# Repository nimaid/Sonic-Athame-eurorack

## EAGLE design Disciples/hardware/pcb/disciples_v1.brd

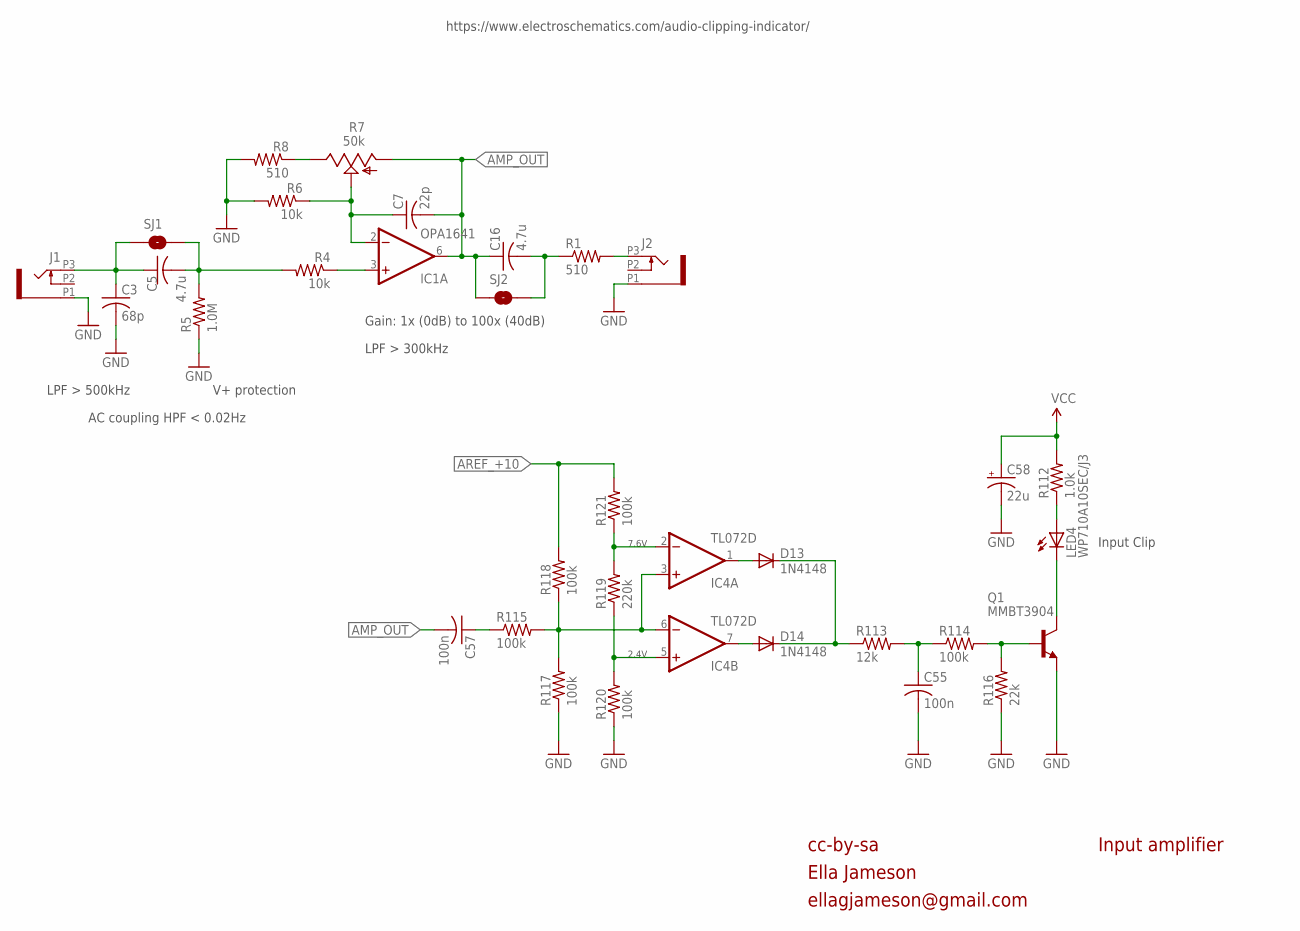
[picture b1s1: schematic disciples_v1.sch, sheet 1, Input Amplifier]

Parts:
C3: 68p; C0402
C5, C16: 4.7u; C0603
C7: 22p; C0402
C55, C57: 100n; C0603
C58: 22u; PANASONIC_C
D13, D14: 1N4148; SOD323-W
IC1: OPA1641; MSOP8
IC4: TL072D; SO08
J1, J2: PJ301_THONKICONN6; WQP_PJ_301M6
LED4: WP710A10SEC/J3; LED3MM
Q1: MMBT3904; SOT23-BEC
R1, R8: 510; R0402
R4, R6: 10k; R0402
R5: 1.0M; R0402
R7: 50k; ALPS_POT_VERTICAL_PS
R112: 1.0k; R0603
R113: 12k; R0603
R114, R115, R117, R118, R120, R121: 100k; R0603
R116: 22k; R0603
R119: 220k; R0603
SJ1, SJ2: SOLDERJUMPERNC; SJ_2S

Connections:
AMP_OUT: C7.2, C16.1, C57.2, IC1.6 (OUT), R7.P$3 (A), SJ2.1; also elsewhere on the board
AREF_+10: R118.2, R121.2; also elsewhere on the board
GND: C3.2, C55.2, C58.-, J1.P1 (1), J2.P1 (1), Q1.E, R5.1, R6.2, R8.2, R116.1, R117.1, R120.1; also elsewhere on the board
unnamed: IC1.3 (+IN), R4.1
unnamed: J2.P3 (3), R1.2
unnamed: C3.1, C5.1, J1.P3 (3), SJ1.1
unnamed: C7.1, IC1.2 (-IN), R6.1, R7.P$2 (S)
unnamed: C5.2, R4.2, R5.2, SJ1.2
unnamed: R7.P$1 (E), R8.1
unnamed: C16.2, R1.1, SJ2.2
unnamed: LED4.K (C), Q1.C
unnamed: C57.1, R115.1
unnamed: IC4.3 (+IN), IC4.6 (-IN), R115.2, R117.2, R118.1
unnamed: IC4.2 (-IN), R119.2, R121.1
unnamed: C55.1, R113.2, R114.1
unnamed: IC4.5 (+IN), R119.1, R120.2
unnamed: D13.A, IC4.1 (OUT)
unnamed: D14.A, IC4.7 (OUT)
unnamed: D13.C, D14.C, R113.1
unnamed: LED4.A, R112.1
unnamed: Q1.B, R114.2, R116.2
VCC: C58.+, R112.2; also elsewhere on the board

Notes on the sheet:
cc-by-sa
Input amplifier
Gain: 1x (0dB) to 100x (40dB)
LPF > 500kHz
V+ protection
LPF > 300kHz
AC coupling HPF < 0.02Hz
Ella Jameson
ellagjameson@gmail.com
2.4V
7.6V
Input Clip
https://www.electroschematics.com/audio-clipping-indicator/

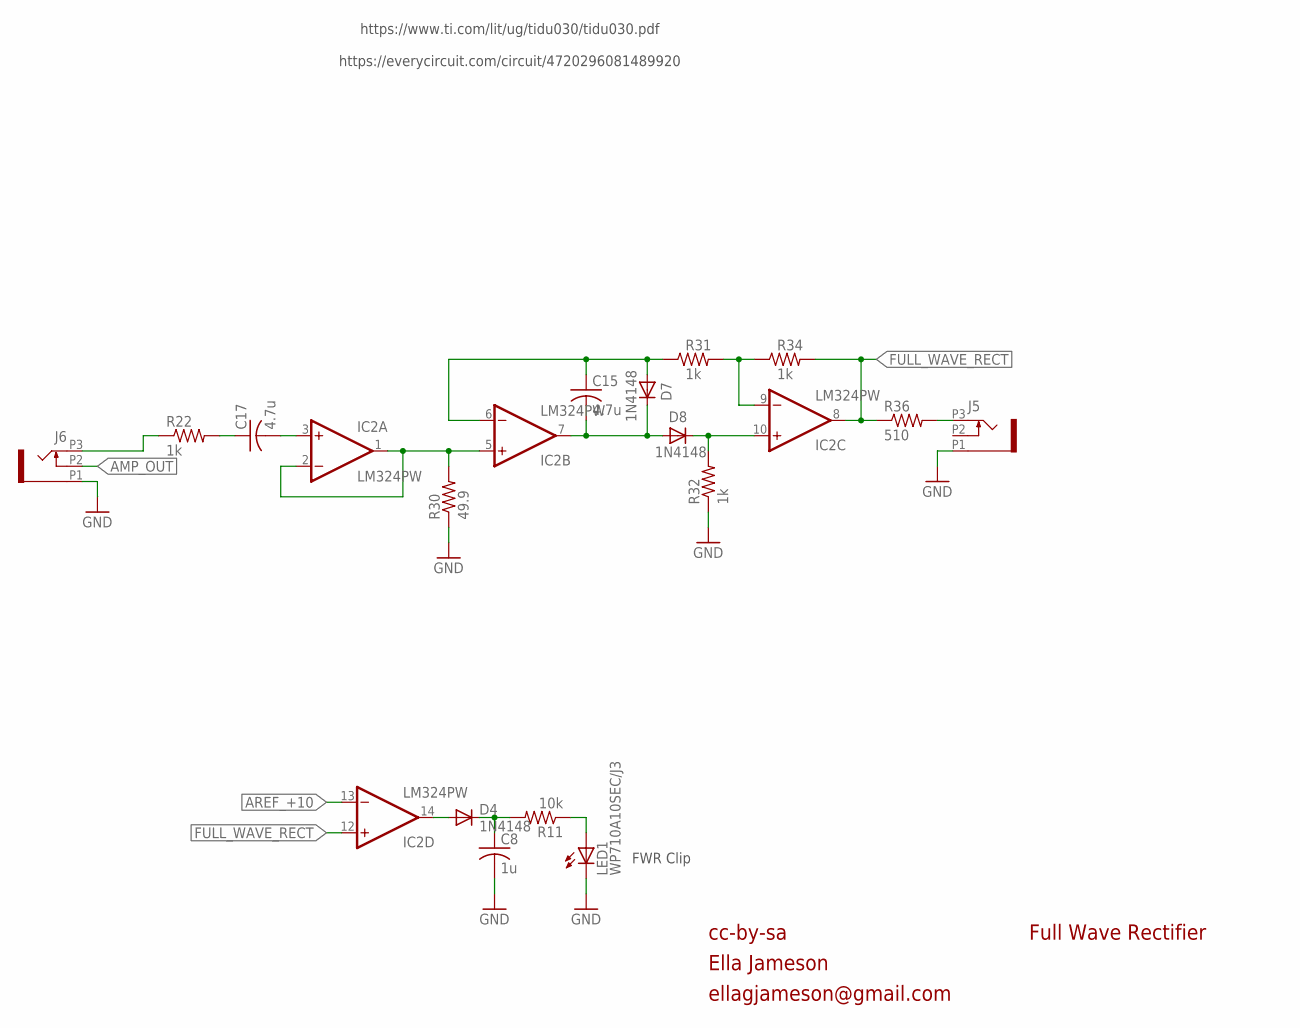
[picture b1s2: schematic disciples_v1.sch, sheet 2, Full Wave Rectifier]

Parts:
C8: 1u; C0402
C15, C17: 4.7u; C0603
D4, D7, D8: 1N4148; SOD523
IC2: LM324PW; TSSOP14
J5, J6: PJ301_THONKICONN6; WQP_PJ_301M6
LED1: WP710A10SEC/J3; LED3MM
R11: 10k; R0402
R22, R31, R32, R34: 1k; R0402
R30: 49.9; R0402
R36: 510; R0402

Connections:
AMP_OUT: J6.P2 (2); also elsewhere on the board
AREF_+10: IC2.13 (-IN); also elsewhere on the board
FULL_WAVE_RECT: IC2.8 (OUT), IC2.12 (+IN), R34.2, R36.1; also elsewhere on the board
FWR_CLIP: D4.A, IC2.14 (OUT)
GND: C8.2, J5.P1 (1), J6.P1 (1), LED1.K (C), R30.1, R32.1; also elsewhere on the board
unnamed: C15.2, D7.C, D8.A, IC2.7 (OUT)
unnamed: J5.P3 (3), R36.2
unnamed: C15.1, D7.A, IC2.6 (-IN), R31.1
unnamed: D8.C, IC2.10 (+IN), R32.2
unnamed: IC2.9 (-IN), R31.2, R34.1
unnamed: C17.1, R22.2
unnamed: C8.1, D4.C, R11.2
unnamed: LED1.A, R11.1
unnamed: C17.2, IC2.3 (+IN)
unnamed: IC2.1 (OUT), IC2.2 (-IN), IC2.5 (+IN), R30.2
unnamed: J6.P3 (3), R22.1

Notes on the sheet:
cc-by-sa
Full Wave Rectifier
Ella Jameson
ellagjameson@gmail.com
https://www.ti.com/lit/ug/tidu030/tidu030.pdf https://everycircuit.com/circuit/4720296081489920
FWR Clip

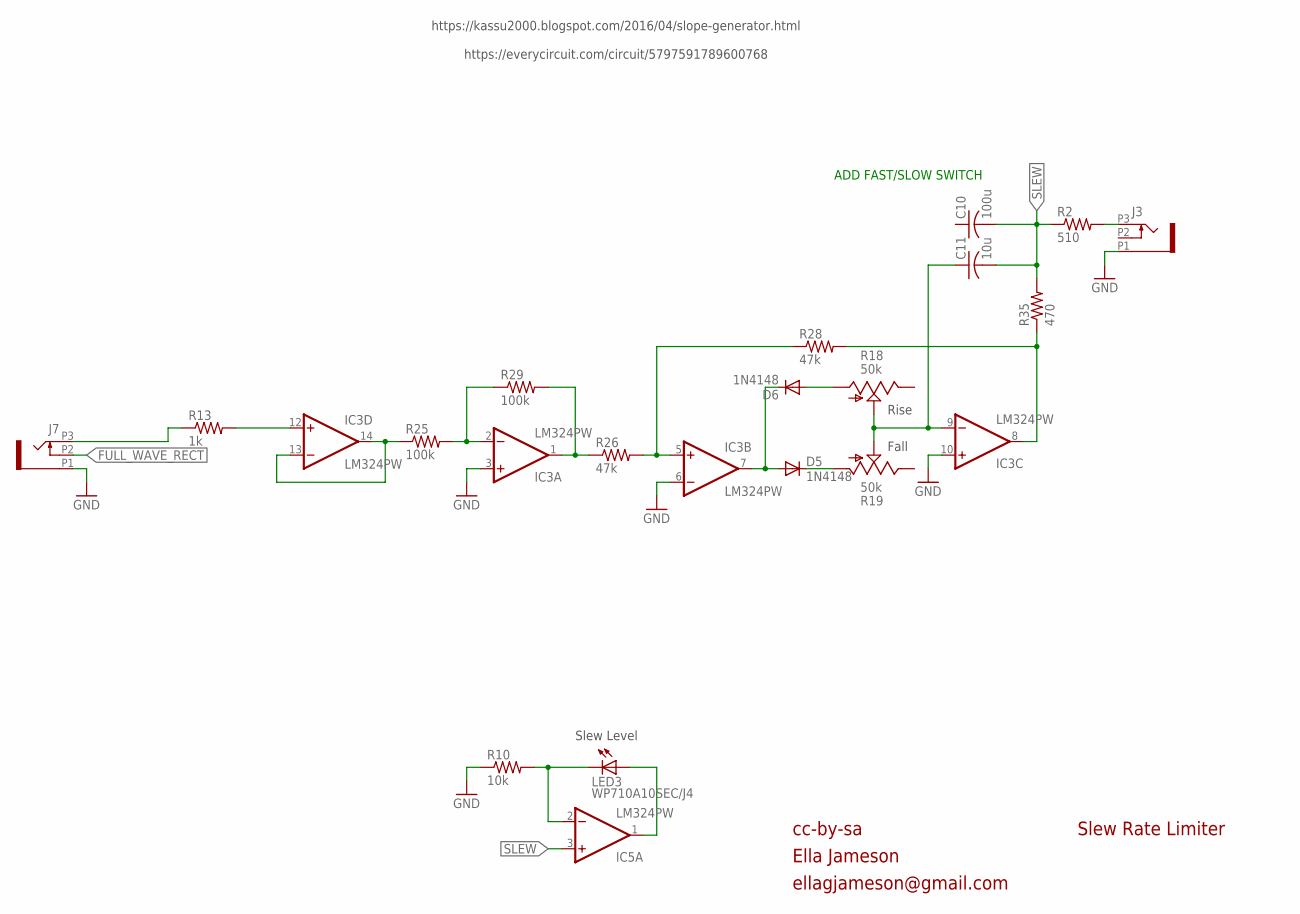
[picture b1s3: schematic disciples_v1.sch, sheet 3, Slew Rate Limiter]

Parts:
C10: 100u; C0402
C11: 10u; C0402
D5, D6: 1N4148; SOD523
IC3, IC5: LM324PW; TSSOP14
J3, J7: PJ301_THONKICONN6; WQP_PJ_301M6
LED3: WP710A10SEC/J4; LED3MM
R2: 510; R0402
R10: 10k; R0402
R13: 1k; R0402
R18, R19: 50k; ALPS_POT_VERTICAL_PS
R25, R29: 100k; R0402
R26, R28: 47k; R0402
R35: 470; R0402

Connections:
FULL_WAVE_RECT: J7.P2 (2); also elsewhere on the board
GND: IC3.3 (+IN), IC3.6 (-IN), IC3.10 (+IN), J3.P1 (1), J7.P1 (1), R10.1; also elsewhere on the board
unnamed: J7.P3 (3), R13.1
unnamed: IC3.13 (-IN), IC3.14 (OUT), R25.1
unnamed: J3.P3 (3), R2.2
unnamed: IC5.2 (-IN), LED3.K (C), R10.2
unnamed: IC3.2 (-IN), R25.2, R29.1
unnamed: IC3.1 (OUT), R26.1, R29.2
unnamed: IC3.5 (+IN), R26.2, R28.1
unnamed: D5.A, D6.C, IC3.7 (OUT)
unnamed: D5.C, R19.P$3 (A)
unnamed: D6.A, R18.P$3 (A)
unnamed: C11.1, IC3.9 (-IN), R18.P$2 (S), R19.P$2 (S)
unnamed: IC3.12 (+IN), R13.2
unnamed: IC5.1 (OUT), LED3.A
unnamed: IC3.8 (OUT), R28.2, R35.1
SLEW: C10.2, C11.2, IC5.3 (+IN), R2.1, R35.2; also elsewhere on the board

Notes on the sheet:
cc-by-sa
Slew Rate Limiter
https://kassu2000.blogspot.com/2016/04/slope-generator.html https://everycircuit.com/circuit/5797591789600768
Ella Jameson
ellagjameson@gmail.com
Fall
Slew Level
Rise
ADD FAST/SLOW SWITCH

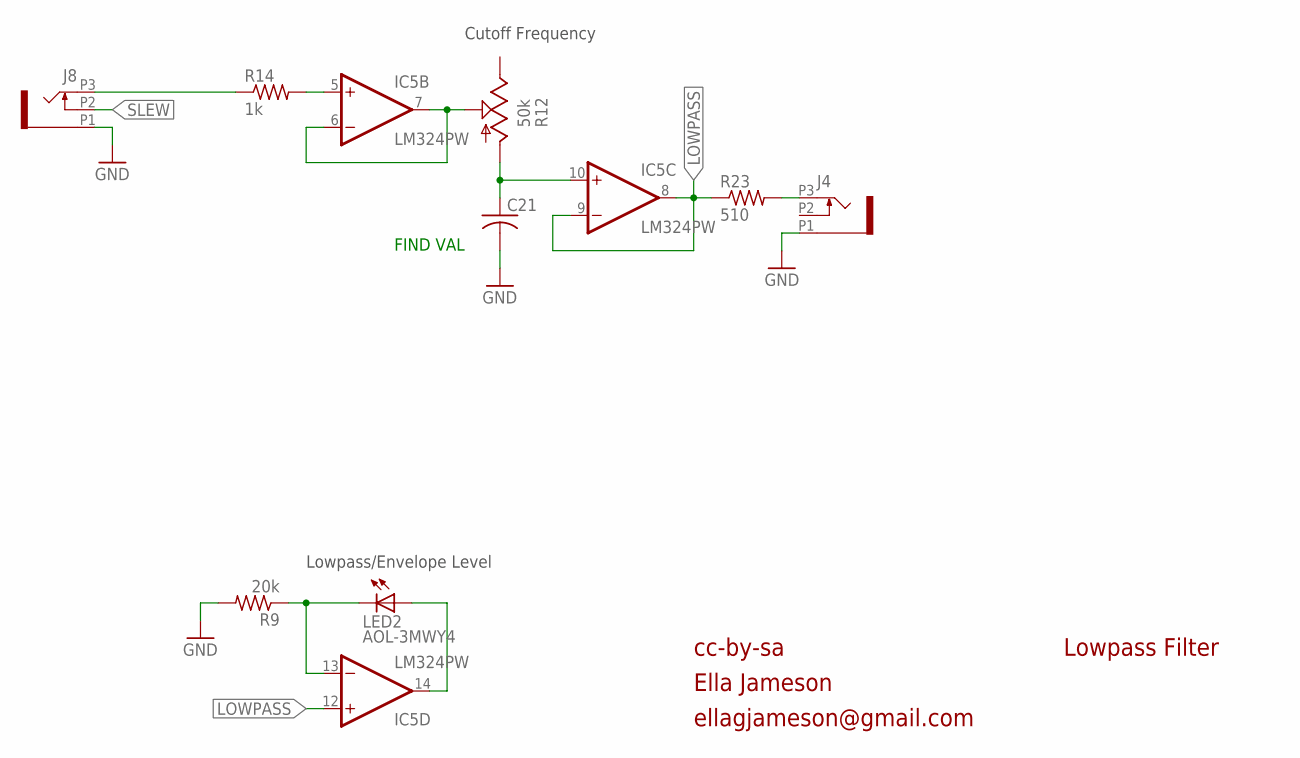
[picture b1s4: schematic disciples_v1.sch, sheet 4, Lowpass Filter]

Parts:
C21: C-USC0402; C0402
IC5: LM324PW; TSSOP14
J4, J8: PJ301_THONKICONN6; WQP_PJ_301M6
LED2: AOL-3MWY4; LED3MM
R9: 20k; R0402
R12: 50k; ALPS_POT_VERTICAL_PS
R14: 1k; R0402
R23: 510; R0402

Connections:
GND: C21.2, J4.P1 (1), J8.P1 (1), R9.2; also elsewhere on the board
LOWPASS: IC5.8 (OUT), IC5.9 (-IN), IC5.12 (+IN), R23.1; also elsewhere on the board
unnamed: C21.1, IC5.10 (+IN), R12.P$3 (A)
unnamed: IC5.5 (+IN), R14.2
unnamed: J8.P3 (3), R14.1
unnamed: J4.P3 (3), R23.2
unnamed: IC5.6 (-IN), IC5.7 (OUT), R12.P$2 (S)
unnamed: IC5.14 (OUT), LED2.A
unnamed: IC5.13 (-IN), LED2.K (C), R9.1
SLEW: J8.P2 (2); also elsewhere on the board

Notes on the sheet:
cc-by-sa
Lowpass Filter
Ella Jameson
ellagjameson@gmail.com
FIND VAL
Lowpass/Envelope Level
Cutoff Frequency

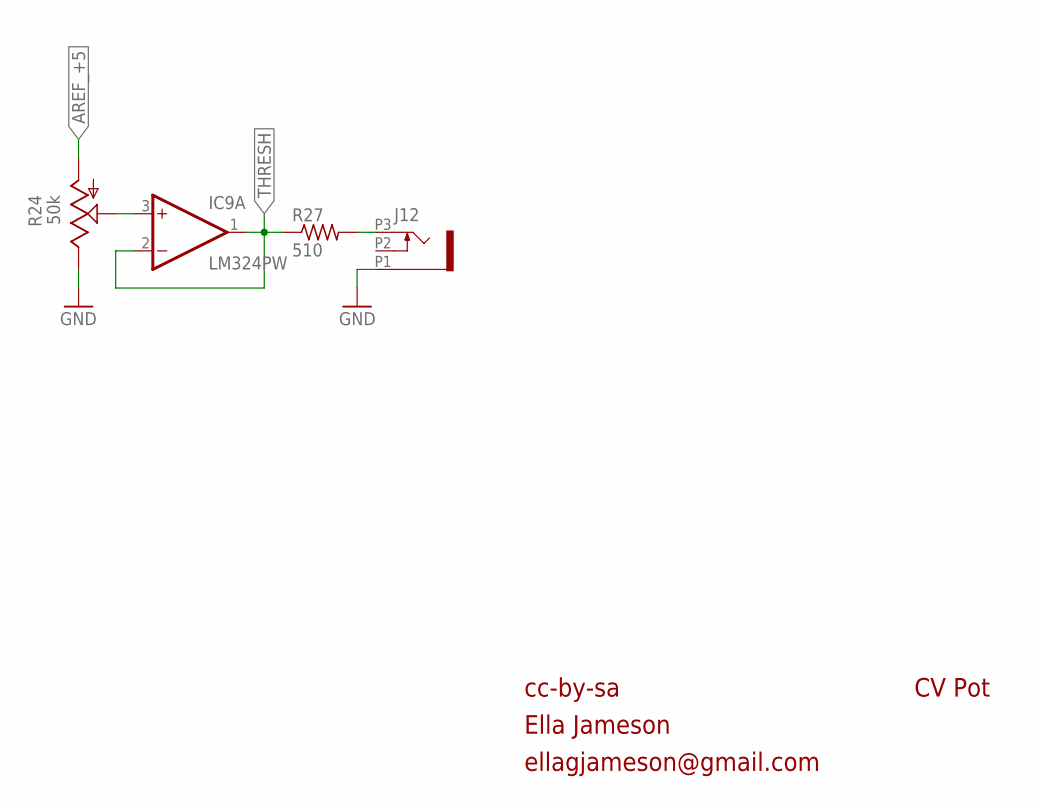
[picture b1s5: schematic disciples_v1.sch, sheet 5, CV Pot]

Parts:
IC9: LM324PW; TSSOP14
J12: PJ301_THONKICONN6; WQP_PJ_301M6
R24: 50k; ALPS_POT_VERTICAL_PS
R27: 510; R0402

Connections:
AREF_+5: R24.P$3 (A); also elsewhere on the board
GND: J12.P1 (1), R24.P$1 (E); also elsewhere on the board
unnamed: IC9.3 (+IN), R24.P$2 (S)
unnamed: J12.P3 (3), R27.2
THRESH: IC9.1 (OUT), IC9.2 (-IN), R27.1; also elsewhere on the board

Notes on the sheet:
cc-by-sa
CV Pot
Ella Jameson
ellagjameson@gmail.com

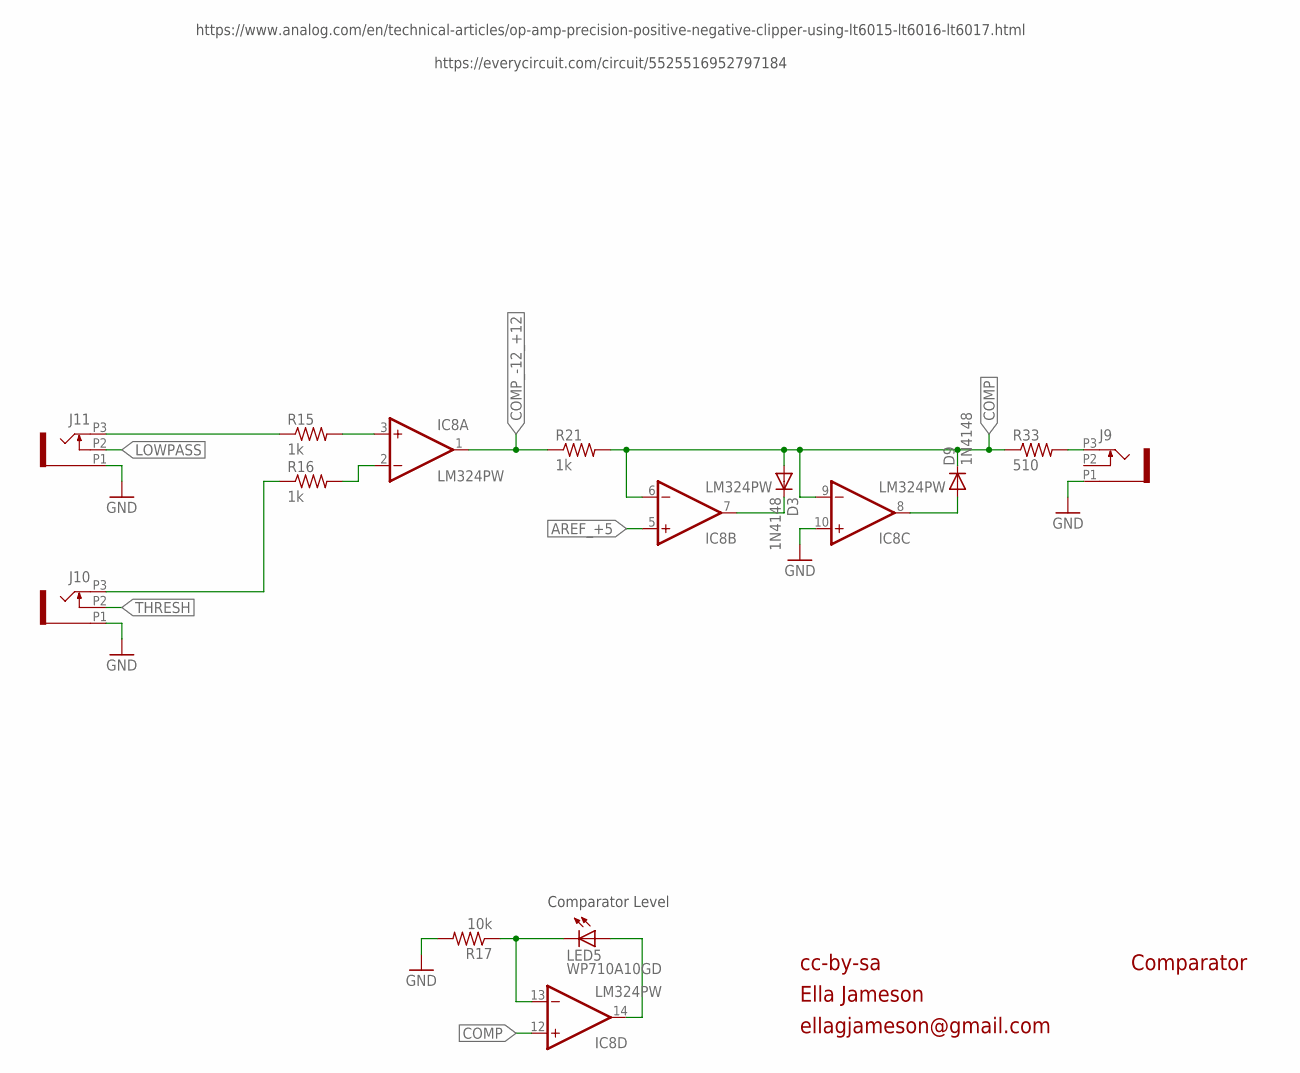
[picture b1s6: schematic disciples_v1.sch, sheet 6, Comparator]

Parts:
D3, D9: 1N4148; SOD523
IC8: LM324PW; TSSOP14
J9, J10, J11: PJ301_THONKICONN6; WQP_PJ_301M6
LED5: WP710A10GD; LED3MM
R15, R16, R21: 1k; R0402
R17: 10k; R0402
R33: 510; R0402

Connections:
AREF_+5: IC8.5 (+IN); also elsewhere on the board
COMP: D3.A, D9.C, IC8.6 (-IN), IC8.9 (-IN), IC8.12 (+IN), R21.2, R33.1
COMP_-12_+12: IC8.1 (OUT), R21.1
GND: IC8.10 (+IN), J9.P1 (1), J10.P1 (1), J11.P1 (1), R17.2; also elsewhere on the board
LOWPASS: J11.P2 (2); also elsewhere on the board
unnamed: J9.P3 (3), R33.2
unnamed: IC8.13 (-IN), LED5.K (C), R17.1
unnamed: IC8.14 (OUT), LED5.A
unnamed: J11.P3 (3), R15.1
unnamed: J10.P3 (3), R16.1
unnamed: IC8.2 (-IN), R16.2
unnamed: IC8.3 (+IN), R15.2
unnamed: D3.C, IC8.7 (OUT)
unnamed: D9.A, IC8.8 (OUT)
THRESH: J10.P2 (2); also elsewhere on the board

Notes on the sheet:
cc-by-sa
Comparator
Ella Jameson
ellagjameson@gmail.com
Comparator Level
https://www.analog.com/en/technical-articles/op-amp-precision-positive-negative-clipper-using-lt6015-lt6016-lt6017.html https://everycircuit.com/circuit/5525516952797184

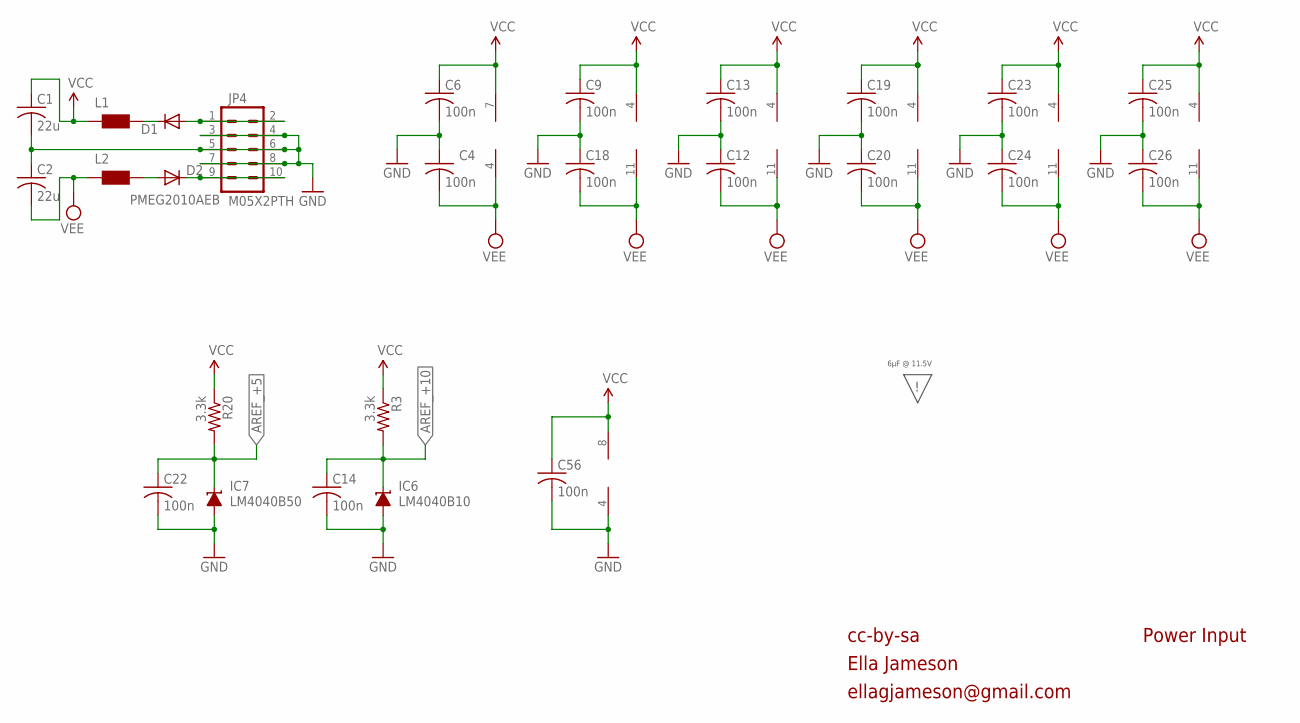
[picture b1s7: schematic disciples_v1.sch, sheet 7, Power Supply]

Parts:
C1, C2: 22u; C1206
C4, C6, C9, C12, C13, C18, C19, C20, C23, C24, C25, C26: 100n; C0402
C14, C22, C56: 100n; C0603
D1, D2: PMEG2010AEB; SOD523
IC1: OPA1641; MSOP8
IC2, IC3, IC5, IC8, IC9: LM324PW; TSSOP14
IC4: TL072D; SO08
IC6: LM4040B10; DBZ_R-PDSO-G3
IC7: LM4040B50; DBZ_R-PDSO-G3
JP4: M05X2PTH; AVR_ICSP
L1, L2: WE-CBF_0603; 0603
R3, R20: 3.3k; R0603

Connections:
AREF_+5: C22.1, IC7.1 (C), R20.2; also elsewhere on the board
AREF_+10: C14.1, IC6.1 (C), R3.2; also elsewhere on the board
GND: C1.2, C2.1, C4.1, C6.2, C9.2, C12.1, C13.2, C14.2, C18.1, C19.2, C20.1, C22.2, C23.2, C24.1, C25.2, C26.1, C56.2, IC4.4 (V-), IC6.2 (A), IC7.2 (A), JP4.3, JP4.4, JP4.5, JP4.6, JP4.7, JP4.8; also elsewhere on the board
unnamed: D1.A, JP4.1, JP4.2
unnamed: D2.C, JP4.9, JP4.10
unnamed: D1.C, L1.2
unnamed: D2.A, L2.2
VCC: C1.1, C6.1, C9.1, C13.1, C19.1, C23.1, C25.1, C56.1, IC1.7 (V+), IC2.4 (V+), IC3.4 (V+), IC4.8 (V+), IC5.4 (V+), IC8.4 (V+), IC9.4 (V+), L1.1, R3.1, R20.1; also elsewhere on the board
VEE: C2.2, C4.2, C12.2, C18.2, C20.2, C24.2, C26.2, IC1.4 (V-), IC2.11 (V-), IC3.11 (V-), IC5.11 (V-), IC8.11 (V-), IC9.11 (V-), L2.1

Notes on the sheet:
cc-by-sa
Power Input
6µF @ 11.5V
Ella Jameson
ellagjameson@gmail.com

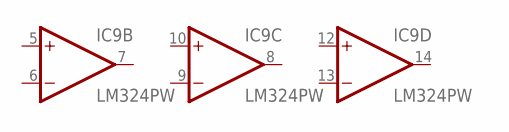
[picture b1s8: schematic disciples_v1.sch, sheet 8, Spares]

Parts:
IC9: LM324PW; TSSOP14

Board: 2 copper layers, 120 parts (2 on the bottom side), 78 nets, no tracks yet.

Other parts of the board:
U$2: ROHS

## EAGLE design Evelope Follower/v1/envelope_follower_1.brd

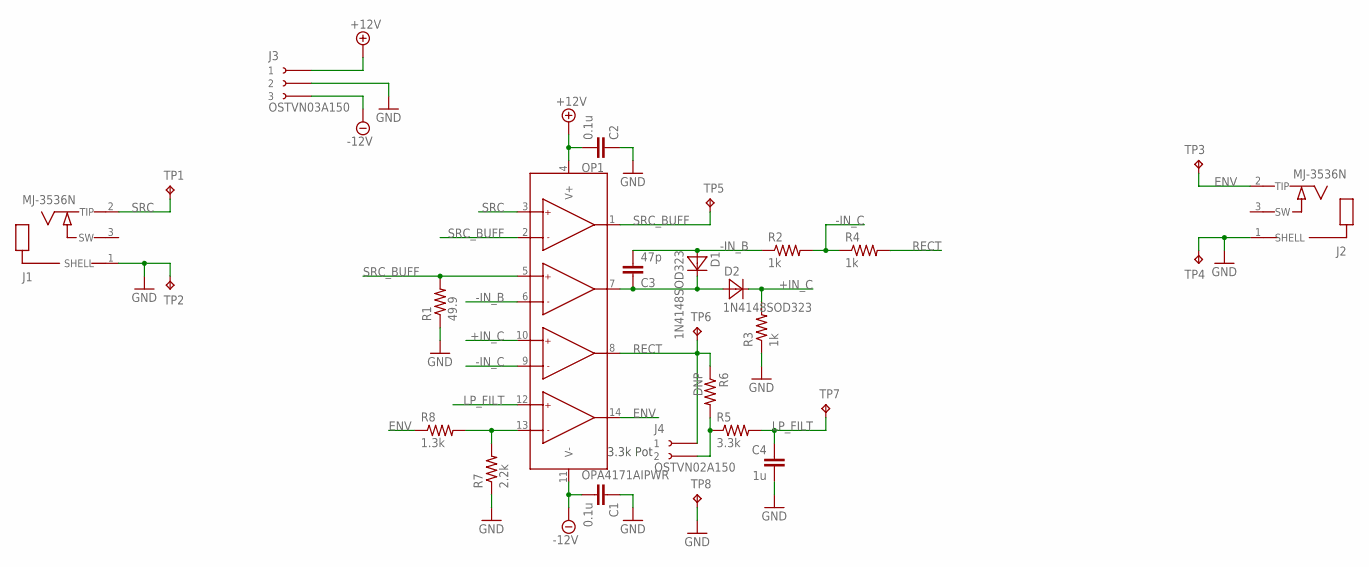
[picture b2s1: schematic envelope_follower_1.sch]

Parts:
C1, C2: 0.1u; C0603
C3: 47p; C0603
C4: 1u; C0603
D1, D2: 1N4148SOD323; SOD323
J1, J2: MJ-3536N
J3: OSTVN03A150
J4: OSTVN02A150
OP1: OPA4171AIPWR; SOP65P640X120-14
R1: 49.9; R0603
R2, R3, R4: 1k; R0603
R5: 3.3k; R0603
R6: DNP; R0603
R7: 2.2k; R0603
R8: 1.3k; R0603
TP1, TP2, TP3, TP4, TP5, TP6, TP7, TP8: TP_THM_1.6_S

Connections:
+12V: C2.2, J3.P$1 (1), OP1.4 (V+)
+IN_C: D2.C, OP1.10 (+IN_C), R3.2
-12V: C1.2, J3.P$3 (3), OP1.11 (V-)
-IN_B: C3.2, D1.A, OP1.6 (-IN_B), R2.1
-IN_C: OP1.9 (-IN_C), R2.2, R4.1
ENV: J2.2 (TIP), OP1.14 (OUT_D), R8.1, TP3.P$1
GND: C1.1, C2.1, C4.2, J1.1 (SHELL), J2.1 (SHELL), J3.P$2 (2), R1.1, R3.1, R7.1, TP2.P$1, TP4.P$1, TP8.P$1
LP_FILT: C4.1, OP1.12 (+IN_D), R5.2, TP7.P$1
unnamed: C3.1, D1.C, D2.A, OP1.7 (OUT_B)
unnamed: J4.P$2 (2), R5.1, R6.2
unnamed: OP1.13 (-IN_D), R7.2, R8.2
RECT: J4.P$1 (1), OP1.8 (OUT_C), R4.2, R6.1, TP6.P$1
SRC: J1.2 (TIP), OP1.3 (+IN_A), TP1.P$1
SRC_BUFF: OP1.1 (OUT_A), OP1.2 (-IN_A), OP1.5 (+IN_B), R1.2, TP5.P$1

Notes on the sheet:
3.3k Pot

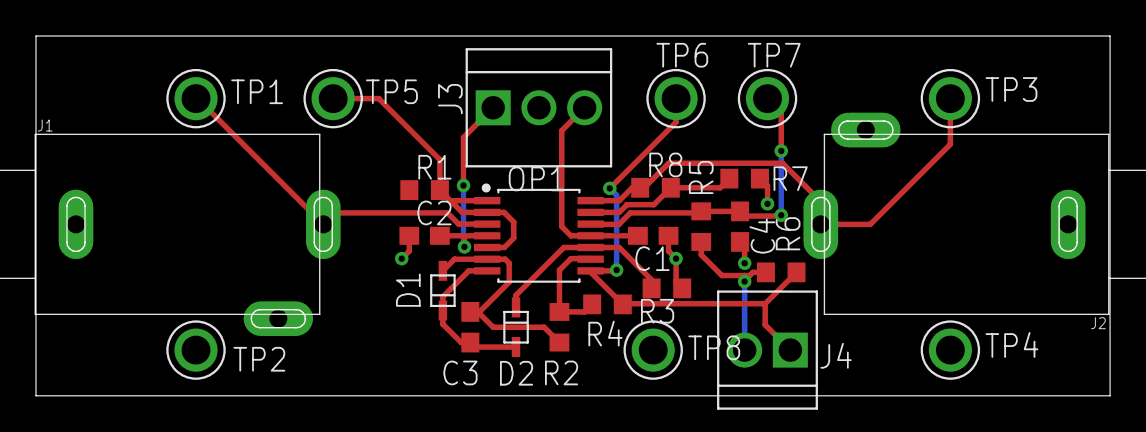
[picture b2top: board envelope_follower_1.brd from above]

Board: 2 copper layers, 59.7 x 20.0 mm, 27 parts (0 on the bottom side), 14 nets.

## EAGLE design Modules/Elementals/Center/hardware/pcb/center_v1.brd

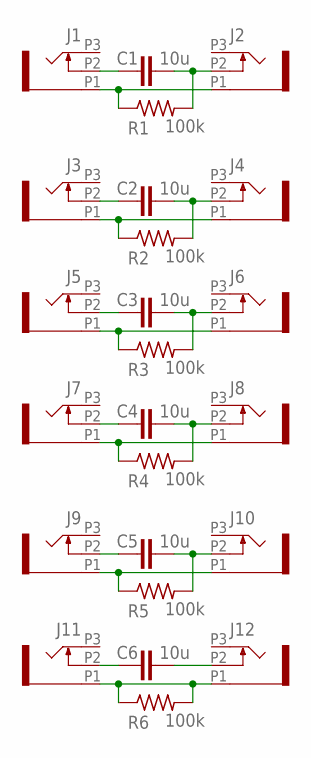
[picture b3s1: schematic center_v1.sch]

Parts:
C1, C2, C3, C4, C5, C6: 10u; C050-024X044
J1, J2, J3, J4, J5, J6, J7, J8, J9, J10, J11, J12: WQP-PJ398SM6; WQP_PJ_301M6
R1, R2, R3, R4, R5, R6: 100k; 0207/2V

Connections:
unnamed: C1.1, J1.P2 (2)
unnamed: C1.2, J2.P2 (2), R1.2
unnamed: J1.P1 (1), J2.P1 (1), R1.1
unnamed: C2.1, J3.P2 (2)
unnamed: C2.2, J4.P2 (2), R2.2
unnamed: J3.P1 (1), J4.P1 (1), R2.1
unnamed: C3.1, J5.P2 (2)
unnamed: C3.2, J6.P2 (2), R3.2
unnamed: J5.P1 (1), J6.P1 (1), R3.1
unnamed: C4.1, J7.P2 (2)
unnamed: C4.2, J8.P2 (2), R4.2
unnamed: J7.P1 (1), J8.P1 (1), R4.1
unnamed: C5.1, J9.P2 (2)
unnamed: C5.2, J10.P2 (2), R5.2
unnamed: J9.P1 (1), J10.P1 (1), R5.1
unnamed: C6.1, J11.P2 (2)
unnamed: C6.2, J12.P2 (2)
unnamed: J11.P1 (1), J12.P1 (1), R6.1, R6.2

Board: 2 copper layers, 24 parts (0 on the bottom side), 18 nets, no tracks yet.

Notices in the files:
Disciples/hardware/pcb/disciples_v1.brd:
cc-by-sa Émilie Gillet, 2016.
cc-by-sa Tom Whitwell, 2014.
